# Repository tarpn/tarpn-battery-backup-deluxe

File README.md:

# TARPN Battery Backup Deluxe

An open source DC-DC Uninterrupted Power Supply for TARPN. 

📖 Click here for [Operation Manual](https://github.com/tarpn/tarpn-battery-backup-deluxe/wiki/Operation-Manual) 📖

Battery Backup Deluxe (BBD) is a system that monitors and switches DC power between a 
power supply and a battery. It is a bespoke power management solution for multi-port packet
radio nodes in the [TARPN project](http://tarpn.net). It is also generally useful for any 12V
systems including non-TARPN Amateur Radio activities.

Supported Features:
* High current capability (30A continuous)
* Automatic switchover to battery
* Battery protection (low/high voltage cutoff)
* Over-temperature cutoff
* Separate switching of critical loads power for priority devices (3A max)
* Safe shutdown procedure of RaspberryPi

Experimental Features:
* Battery charging

Non-Features:
* Load distribution or fusing
* Integration with battery chargers (AC/DC chargers, or solar charge controllers)

Two custom PCBs are employed for voltage sensing, switching, and control. The two boards are
referred to as the Power Board and the Control Board. The Power Board connects to a regulated
DC power supply, a 12V battery, a 12V load, a DC buck regulator for a RaspberryPi, and the Control Board. 
The Control Board connects to a RaspberryPi using a communication cable. 

# Images

Power Board, bare PCB

Power Board, assembled and installed

# PCB Overview

Power board layout

```
 -[B]--[L]--[S]--[N]--[N]--[N]-
|  |    |    |                 |
|  |~S2~ ~S1~               [C]|
|  |                           |
|   ~ ~ ~ ~ ~ ~ ~ ~ ~ ~ S3     |
|                        |     |
 -----------------------[P][N]-
```

Labels:

* B: Battery Positive
* S: Supply Positive
* L: Load Positive
* N: Common Grounds
* P: Critical Load Positive
* S1: Supply Switch
* S2: Battery Switch
* S3: Critical Load Switch
* C: 12-pin connector to control board

Three p-channel mosfet switches are utilized to connect various loads to one of two DC power sources. 
Loads connected to the "L" terminal are either connected to the Power Supply "S" via S1, the Battery 
"B" via S2, or they are disconnected. A separate low power switch S3 is used for critical loads, 
such as a RaspberryPi or other low power control circuits.

S1 and S2 are high powered DPAK mosfets with a very low on-resistance.

All connected supplies and loads share a common ground. This ground is also shared with the control board. 
If a RaspberryPi (or other device) is monitoring the serial output of the control board, it must also share
this common ground.

Control board layout

```
 ------------------------------
|         ___________      ___  |
|[C]     |   OLED    |    | R | |
|         -----------      ---  |
|    [RPi]               [ICSP] |
 ------------------------------
```

Labels:

* C: 12-pin connector to power board
* RPi: 10-pin connector to Raspberry Pi
* ICSP: Programming header for ATMega
* OLED: 128x32 OLED display
* R: Rotary encoder with switch

# Control Board Modes

The digital electronics on the power board, the 5V regulator for the Control Board, and the critical load
output are powered directly by the battery. 

## Standby

When a power supply is attached and supplying a sufficient voltage, the system will be in Standby mode. 
Loads are powered by the power supply through S1.

* S1: closed
* S2: open
* S3: closed

## Backup

If a low voltage is detected on the power supply, the loads are transferred to the battery. This switching
time is typically in the microsecond range. The ability of the loads to maintain sufficient voltage during
the switching time is dependent on the load current and the available standby capacitance. 
C1 on the power board can be populated with a reasonably large (1000µF range) bulk capacitor. 

* S1: open 
* S2: closed
* S3: closed

## Recovery

Once in the Backup state, the system will enter the Recovery state if a sufficient voltage is seen at the
power supply input. To avoid oscillations, the system will remain in the Recovery state for a configured
number of milliseconds before transitioning to Standby.

* S1: open 
* S2: closed
* S3: closed

## Faults

The system monitors battery voltage to protect the loads from over-voltage and to protect the battery from
under-voltage. In these two cases, the battery is disconnected from the loads.

A temperature sensor is used to monitor the temperature of the PCB near the mosfet switches. If a high
temperature is detected, the switches are both opened to prevent the mosfets from over-heating and failing.

* S1: open 
* S2: open
* S3: closed

# Tuning

To account for variability of components used by the sensor circuits, the firmware includes several "tunables".

* X1: Current Sense. A scaling factor for the current shunt resistor R3. It should be set to 0.04 (20 * R3)
* X2: Current Offset. A voltage offset provided by the reference voltage U1. It should be set to 2.486
* X3: ADC Reference. A voltage reference provided by U5. Measured from AREF (typically 4.860)
* X4: Voltage Factor. A scaling factor for the two resistor divider networks R1+R4 and R8+R11. It should be set to R4 / (R1 + R4).
* X5: Voltage Offset. A voltage offset for the resistor divider networks. Set this to 0.0
* X6: Battery Factor. The same as X1, but for R36 (this may be deprecated in the future)
* X7: Battery Offset. The same as X2, but for the battery current shunt (this may be deprecated in the future)

# Configuration

TODO

# RaspberryPi Interface

J8 on the control board connects to pins 1 through 10 on the RaspberryPi. 

| Pin | RPi signal | Control board signal |
| --- | ---------- | -------------------- |
| 1   | +3V3       | used for pullup of pin 5 |
| 2   | +5V        | unused |
| 3   | GPIO 2     | RPI_PWR (active low) |
| 4   | +5V        | unused |
| 5   | GPIO 3     | RPI_SHUTDOWN (active low) |
| 6   | Ground     | Ground |
| 7   | GPIO 4     | Reset† |
| 8   | GPIO 14    | RXD (serial) |
| 9   | Ground     | Ground |
| 10  | GPIO 15    | TXD (serial) |

† This pin is sometimes cut on older TARPN installations. See below for workaround instructions.

The RPI_SHUTDOWN signal is used to trigger a shutdown of the RPi. When this signal is momentarily pulled low the RPi 
will perform a safe shutdown. A pull-up resistor between RPi pin 5 and RPi pin 1 is used to prevent this
signal from floating.

The RPI_PWR is used to inform the control board whether or not the RPi has power. When this signal is
low, the RPi is powered on. This signal allows the control board to determine when the RPi has powered off 
following a safe shutdown.

RXD and TXD are used for serial communication from the control board to the RPi. This is used for exporting
telemetry from the control board.

If pin 7 has been cut, a separate jumper between an unused GPIO on the RPi and the RESET line on the control 
board will be needed. Pin 5 of the ISCP header can be used to solder one end of a jumper. When doing firmware
uploads from the RPi, a different reset pin can be selected with the `--gpio` argument.

## RPi Hardware Modification

To accommodate the 10 pin ribbon connector on the RPi, pins 11 and 12 must be snipped or bent out of the way.

## RPi Hardware Configuration

To enable the functions of RPI_SHUTDOWN and RPI_PWR, two special configurations are needed on the RPi.
In the `/boot/config.txt` file, add the following lines below the comment 
`# Additional overlays and parameters are documented /boot/overlays/README`:

```
dtoverlay=gpio-poweroff,gpiopin=2,active_low=1
dtoverlay=gpio-shutdown,gpio_pin=3,active_low=1,gpio_pull=up
```

The hardward UART must also be enabled for communication with the control board. At the bottom of `/boot/config.txt`, add

```
[all]
enable_uart=1
```

This can be done when preparing the SD card or on a running RPi. If done on a running RPi, a reboot is necessary for the 
changes to take affect.

## RPi Software Setup

Assuming a starting point of Raspberry Pi OS (Debian Bullseye or Bookworm), we need to install a few dependencies.

```
sudo apt-get -y install python3-pip python3-venv supervisor prometheus prometheus-node-exporter lsof avrdude
```

Configure supervisor to be run as the "pi" user. Modify the file `/etc/supervisor/supervisord.conf` to add a "chown"
to the "unix_http_server" section:

```
[unix_http_server]
file=/var/run/supervisor.sock   ; (the path to the socket file)
chmod=0700                      ; sockef file mode (default 0700)
chown=pi:pi                     
```

Restart supervisor service
```
sudo service supervisor restart
```

Confirm supervisor is running and accessible

```
supervisorctl pid
```

Should return the PID (Process ID) of the supervisord program.

### Install tarpn-bbd Python package

Create an installation directory under `/opt` and install a Python environment into it.

_These instructions assume an installation directory of /opt/tarpn. However, the software can be installed at any location_

```
sudo mkdir /opt/tarpn
sudo chown pi:pi /opt/tarpn
python3 -m venv /opt/tarpn
```

Install the `tarpn-bbd-agent` program into the newly created Python environment

```
/opt/tarpn/bin/pip install --upgrade --index-url https://pypi.mumrah.synology.me/simple tarpn-bbd-agent
```

This will install the program and create several directories under `/opt/tarpn`. 

### Configure Supervisor

Once the tarpn-bbd Python package is installed, we can copy a supervisor config into the system's
configuration directory. This will allow for the Python program to be automatically run on RPi startup
and automatically restarted if it encounters a fatal error.

```
sudo cp /opt/tarpn/extra/tarpn-bbd-agent-supervisor.conf /etc/supervisor/conf.d/tarpn-bbd-agent.conf
```

This file tells supervisor how to run the tarpn-bbd-agent program. Issue a "reload" command to tell
supervisor to read this new config file

```
supervisorctl reload
```

Now the agent program should be running. Run "supervisorctl status" to confirm. The output should look like:

```
> supervisorctl status
tarpn-bbd-agent                  RUNNING   pid 15487, uptime 0:00:04
```

Check that the metrics are being exposed over HTTP. Visit http://localhost:9000 on the RPi, or http://<your-rpi-ip-address>:9000
from another computer on your network. You should see a plain text output that looks like:

```
# HELP python_gc_objects_collected_total Objects collected during gc
# TYPE python_gc_objects_collected_total counter
python_gc_objects_collected_total{generation="0"} 327.0
python_gc_objects_collected_total{generation="1"} 81.0
python_gc_objects_collected_total{generation="2"} 0.0
```

Next, check that the node metrics are being exposed by the prometheus-node-exporter. Visit http://localhost:9100
or http://<your-rpi-ip-address>:9100. This will have a lot more output than the other exporter. Here is a snippet

```
# HELP node_cpu_seconds_total Seconds the CPUs spent in each mode.
# TYPE node_cpu_seconds_total counter
node_cpu_seconds_total{cpu="0",mode="idle"} 2883.87
node_cpu_seconds_total{cpu="0",mode="iowait"} 5.04
node_cpu_seconds_total{cpu="0",mode="irq"} 0
node_cpu_seconds_total{cpu="0",mode="nice"} 0
node_cpu_seconds_total{cpu="0",mode="softirq"} 0.95
node_cpu_seconds_total{cpu="0",mode="steal"} 0t
node_cpu_seconds_total{cpu="0",mode="system"} 11.35
node_cpu_seconds_total{cpu="0",mode="user"} 22.08
```

### Python Configuration

The default configuration should work on most installations, but if a different serial port or HTTP port is needed, 
it can be changed in `/opt/tarpn/config/bbd.ini`

```
[default]
log.dir = /opt/tarpn/logs
log.config = config/logging.ini
serial.port = /dev/ttyS0
serial.speed = 38400
prometheus.port = 9000
```

After re-configuring, restart the service with supervisor

```
supervisorctl restart tarpn-bbd-agent
```

# Monitoring

If desired, a metrics collection database (Prometheus) and dashboard system (Grafana) can be used to visualize
the sensor data exported by the control board.

Prometheus needs network access to the RPi running `tarpn-bbd`, and Grafana needs network access to Prometheus.
On a home network, this is usually achieved without any extra effort. It is possible to run the TARPN stack 
(including `tarpn-bbd`) along with Prometheus and Grafana, but it is also possible to run Prometheus and Grafana
on a separate server if resources of the RPi become constained.

## Prometheus Configuration

Prometheus is an efficient time-series database that is optimized for metrics collection. By default, Prometheus 
is installed on the RPi that is also running TARPN and the Python agent. If desired, Prometheus can also be 
installed on another server (RPi or otherwise). Follow the 
[general installation instructions](https://prometheus.io/docs/prometheus/latest/installation/) for this.

Put the prometheus config in place

```
sudo cp /opt/tarpn/extra/prometheus.yml /etc/prometheus/prometheus.yml
```

And restart prometheus

```
sudo service prometheus restart
```

Launch the Prometheus UI and confirm the three targets are "UP". Load the UI by accessing http://localhost:9090 
on a web browser on the RPi, or http://<your-rpi-ip-address>:9090 from a web browser on another computer in your
network.

Click on Status, then Targets

And the three Targets should be in the "UP" State.

## Grafana Install and Configuration

Follow the instructions to [install Grafana OSS](https://grafana.com/tutorials/install-grafana-on-raspberry-pi/#install-grafana).
Grafana can run on the TARPN RPi or on a separate server (RPi or otherwise).

For other installation types, follow the [general installation instructions](https://grafana.com/docs/grafana/latest/setup-grafana/installation/).

Copy some configuration files from the `tarpn-bbd` installation over to Grafana

```
sudo cp /opt/tarpn/extra/grafana.ini /etc/grafana/grafana.ini
sudo cp /opt/tarpn/extra/prometheus-datasource.yml /etc/grafana/provisioning/datasources/prometheus.yml
```

Enable Grafana service (as indicated the Grafana installation output). This will enable Grafana to start
when the RPi starts.

```
sudo /bin/systemctl daemon-reload
sudo /bin/systemctl enable grafana-server
```

Start Grafana (restart if it's already running)
```
sudo service grafana restart
```

Access the Grafana UI at http://localhost:3000 or `http://<your-rpi-ip-address>:3000`. 

Confirm the "prometheus" datasource was created

https://github.com/tarpn/tarpn-battery-backup-deluxe/assets/55116/4cb37a2d-a11b-4c16-b97d-481c0bf3d614

Next, import the dashboard

* Open https://github.com/tarpn/tarpn-battery-backup-deluxe/blob/main/py/extra/grafana-dashboard.json
* Click "Download Raw File"
* Open Grafana UI
* Navigate to Dashboards
* Click New -> Import
* Select the dashboard JSON file
* Select the "Prometheus" datasource we looked at earlier

https://github.com/tarpn/tarpn-battery-backup-deluxe/assets/55116/16305afa-259e-4ca9-8b7f-3a017b2bc0ff

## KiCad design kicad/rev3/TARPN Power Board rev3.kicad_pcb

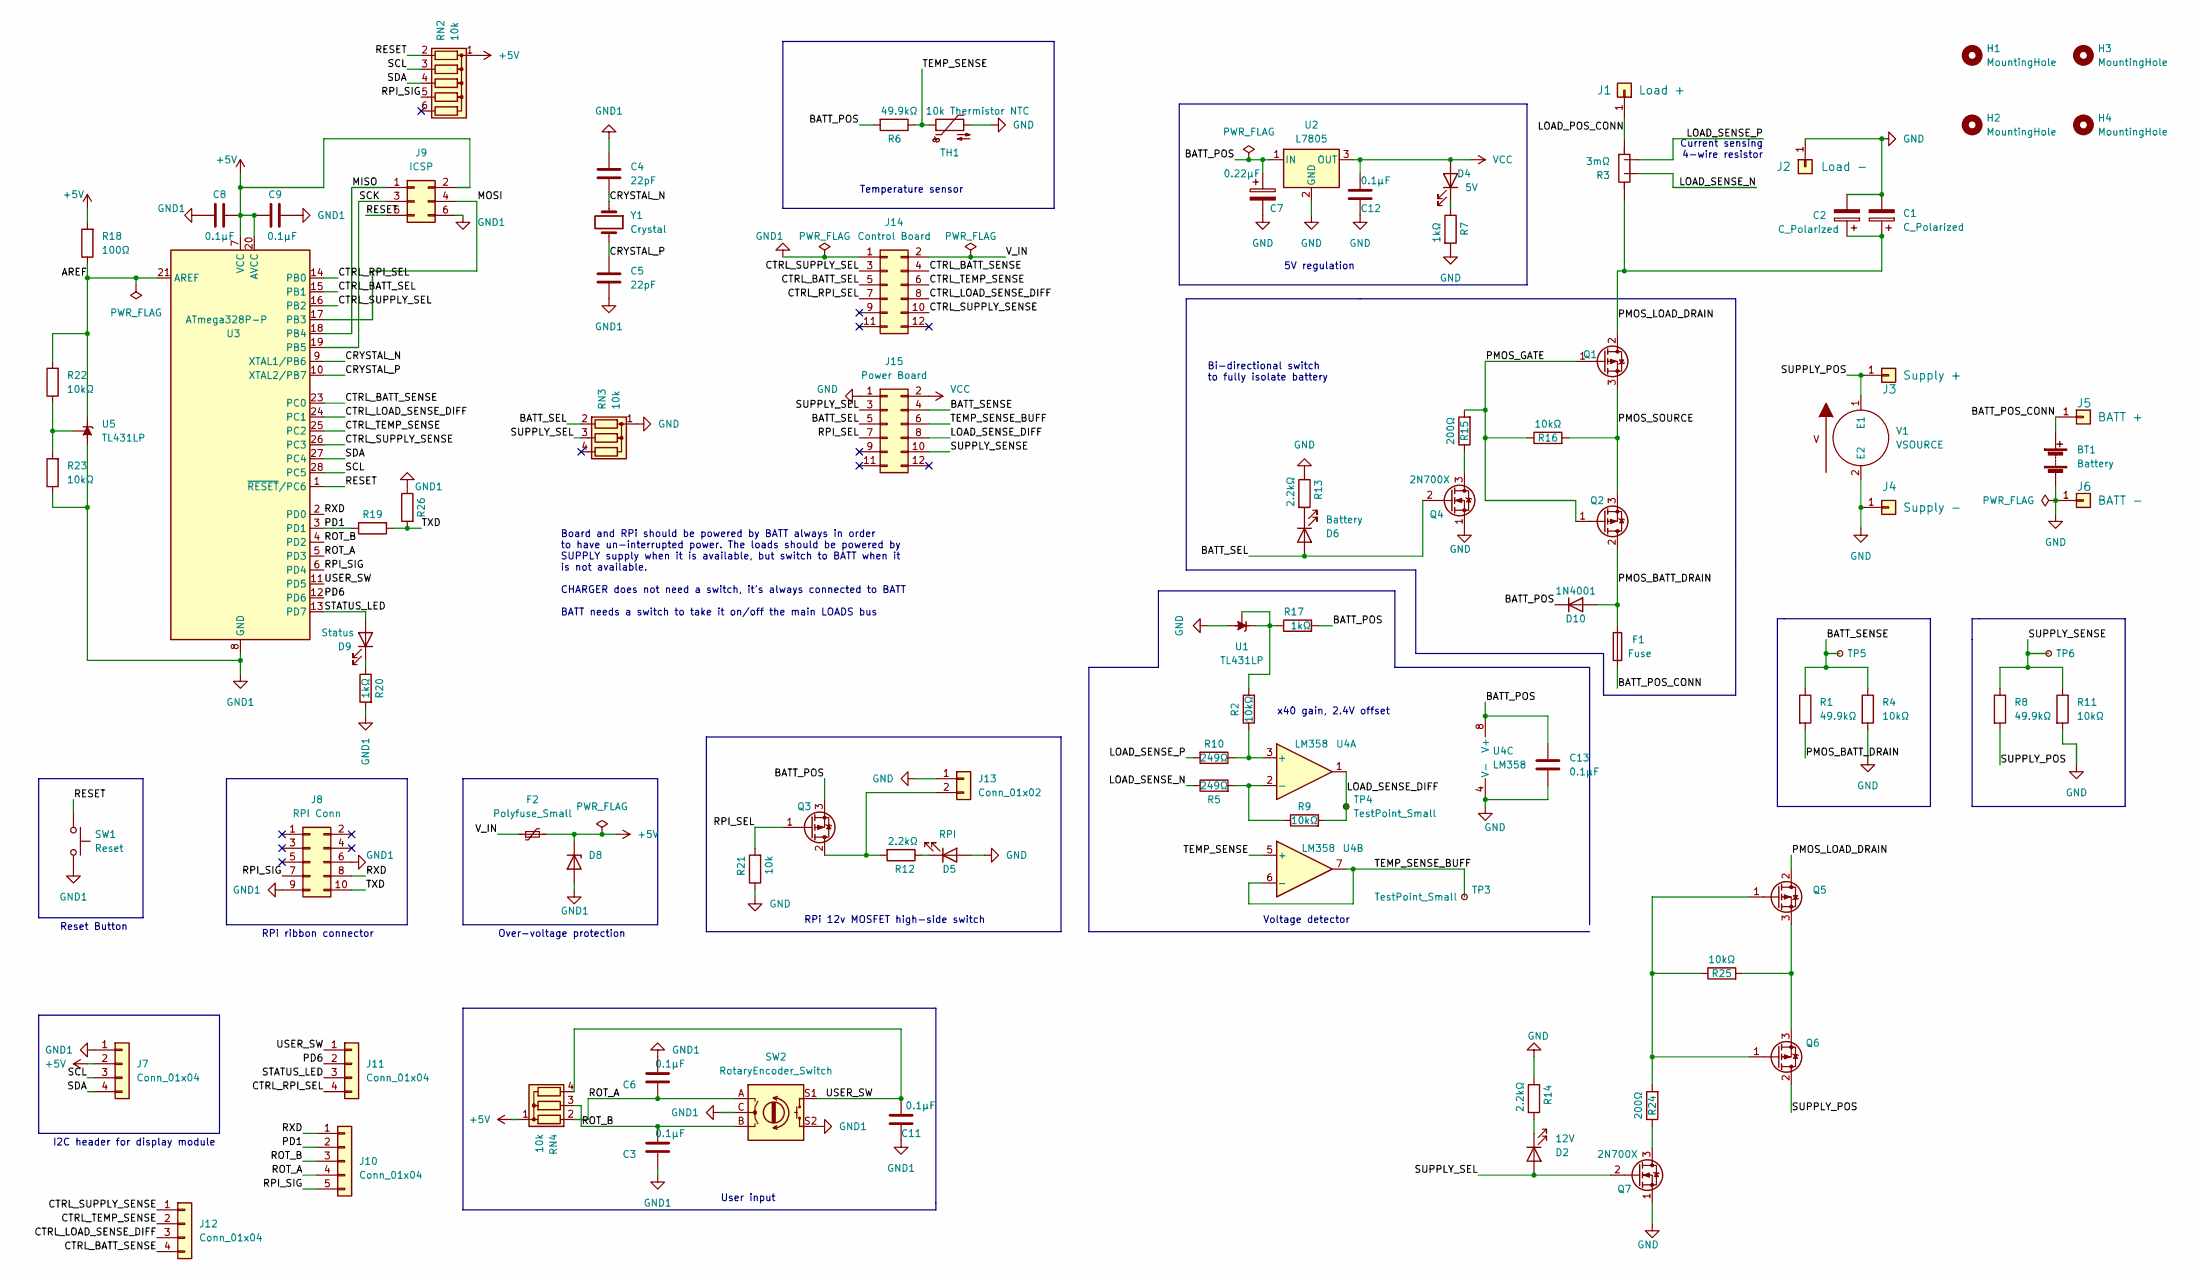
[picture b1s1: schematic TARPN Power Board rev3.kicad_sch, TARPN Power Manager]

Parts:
BT1: Battery
C1, C2: C_Polarized; CP_Radial_D6.3mm_P2.50mm
C3, C6, C8, C9, C11, C12, C13: 0.1µF; C_Disc_D3.0mm_W2.0mm_P2.50mm
C4, C5: 22pF; C_Disc_D3.0mm_W2.0mm_P2.50mm
C7: 0.22µF; CP_Radial_D5.0mm_P2.50mm
D2: 12V; LED_D3.0mm
D4: 5V; LED_D3.0mm
D5: RPI; LED_D3.0mm
D6: Battery; LED_D3.0mm
D8: D_DO-41_SOD81_P3.81mm_Vertical_KathodeUp
D9: Status; LED_D3.0mm
D10: 1N4001; D_DO-41_SOD81_P10.16mm_Horizontal
F1: Fuse; JCASE
F2: Polyfuse_Small; Littlefuse RXEF Series
H1, H2, H3, H4: MountingHole; MountingHole_4.3mm_M4
J1: Load +; B6A-PCB-RS
J2: Load -; B6A-PCB-RS
J3: Supply +; B6A-PCB-RS
J4: Supply -; B6A-PCB-RS
J5: BATT +; B6A-PCB-RS
J6: BATT -; B6A-PCB-RS
J7, J11, J12: Conn_01x04; PinHeader_1x04_P2.54mm_Vertical
J8: RPI Conn; PinHeader_2x05_P2.54mm_Vertical
J9: ICSP; IDC-Header_2x03_P2.54mm_Vertical
J10: Conn_01x04; PinHeader_1x05_P2.54mm_Vertical
J13: Conn_01x02; 691213510002
J14: Control Board; IDC-Header_2x06_P2.54mm_Vertical
J15: Power Board; IDC-Header_2x06_P2.54mm_Vertical
Q1, Q2, Q5, Q6: IRF4905; TO-252-2-ViasHandSolder
Q3: IRF9Z24; TO-220-3_Vertical
Q4, Q7: 2N700X; TO-92_HandSolder
R1, R6, R8: 49.9kΩ; R_Axial_DIN0207_L6.3mm_D2.5mm_P10.16mm_Horizontal
R2, R4, R9, R11, R16, R22, R23, R25: 10kΩ; R_Axial_DIN0207_L6.3mm_D2.5mm_P10.16mm_Horizontal
R3: 3mΩ; R_2512_6332_4_wire
R5, R10: 249Ω; R_Axial_DIN0207_L6.3mm_D2.5mm_P10.16mm_Horizontal
R7, R17, R20: 1kΩ; R_Axial_DIN0207_L6.3mm_D2.5mm_P10.16mm_Horizontal
R12, R13, R14: 2.2kΩ; R_Axial_DIN0207_L6.3mm_D2.5mm_P10.16mm_Horizontal
R15, R24: 200Ω; R_Axial_DIN0207_L6.3mm_D2.5mm_P10.16mm_Horizontal
R18: 100Ω; R_Axial_DIN0207_L6.3mm_D2.5mm_P10.16mm_Horizontal
R19, R26: R_Axial_DIN0207_L6.3mm_D2.5mm_P10.16mm_Horizontal
R21: 10k; R_Axial_DIN0207_L6.3mm_D2.5mm_P10.16mm_Horizontal
RN2: 10k; R_Array_SIP6
RN3, RN4: 10k; R_Array_SIP4
SW1: Reset; SW_PUSH_6mm
SW2: RotaryEncoder_Switch; RotaryEncoder_Alps_EC11E-Switch_Vertical_H20mm
TH1: 10k Thermistor NTC; R_Axial_DIN0204_L3.6mm_D1.6mm_P5.08mm_Horizontal
TP3, TP4, TP5, TP6: TestPoint_Small; TestPoint_THTPad_D1.5mm_Drill0.7mm
U1, U5: TL431LP; TO-92_Inline_Wide
U2: L7805; TO-220-3_Vertical
U3: ATmega328P-P; DIP-28_W7.62mm
U4: LM358
V1: VSOURCE
Y1: Crystal; Crystal_HC49-4H_Vertical

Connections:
+5V: C8.1, C9.2, D8.1 (K), F2.2, J7.2, J9.2, R18.2, RN2.1 (common), RN4.1 (common), U3.7 (VCC), U3.20 (AVCC)
/AREF: R18.1, R22.2, U3.21 (AREF), U5.3 (K)
/BATT_POS: C7.1, C13.2, D10.1 (K), Q3.3 (S), R6.2, R17.2, U2.1 (IN), U4.8 (V+)
/BATT_POS_CONN: BT1.1 (+), F1.2, J5.1
/BATT_SEL: D6.2 (A), J15.5, Q4.2 (G), RN3.2 (R1)
/BATT_SENSE: J15.4, R1.1, R4.1, TP5.1
/CRYSTAL_N: C4.2, U3.9 (XTAL1/PB6), Y1.1
/CRYSTAL_P: C5.1, U3.10 (XTAL2/PB7), Y1.2
/CTRL_BATT_SEL: J14.5, U3.15 (PB1)
/CTRL_BATT_SENSE: J12.4, J14.4, U3.23 (PC0)
/CTRL_LOAD_SENSE_DIFF: J12.3, J14.8, U3.24 (PC1)
/CTRL_RPI_SEL: J11.4, J14.7, U3.14 (PB0)
/CTRL_SUPPLY_SEL: J14.3, U3.16 (PB2)
/CTRL_SUPPLY_SENSE: J12.1, J14.10, U3.26 (PC3)
/CTRL_TEMP_SENSE: J12.2, J14.6, U3.25 (PC2)
/LOAD_POS_CONN: J1.1, R3.1
/LOAD_SENSE_DIFF: J15.8, R9.2, TP4.1, U4.1
/LOAD_SENSE_N: R3.4, R5.1
/LOAD_SENSE_P: R3.3, R10.2
/MISO: J9.1, U3.18 (PB4)
/MOSI: J9.4, U3.17 (PB3)
/PD1: J10.2, R19.1, U3.3 (PD1)
/PD6: J11.2, U3.12 (PD6)
/PMOS_BATT_DRAIN: D10.2 (A), F1.1, Q2.2 (D), R1.2
/PMOS_GATE: Q1.1 (G), Q2.1 (G), R15.2, R16.1
/PMOS_LOAD_DRAIN: C1.1, C2.1, Q1.2 (D), Q5.2 (D), R3.2
/PMOS_SOURCE: Q1.3 (S), Q2.3 (S), R16.2
/RESET: J9.5, RN2.2 (R1), SW1.1, U3.1 (~RESET/PC6)
/ROT_A: C6.2, J10.4, RN4.2 (R1), SW2.A, U3.5 (PD3)
/ROT_B: C3.1, J10.3, RN4.3 (R2), SW2.B, U3.4 (PD2)
/RPI_SEL: J15.7, Q3.1 (G), R21.2
/RPI_SIG: J8.7, J10.5, RN2.5 (R4), U3.6 (PD4)
/RXD: J8.8, J10.1, U3.2 (PD0)
/SCK: J9.3, U3.19 (PB5)
/SCL: J7.3, RN2.3 (R2), U3.28 (PC5)
/SDA: J7.4, RN2.4 (R3), U3.27 (PC4)
/STATUS_LED: D9.2 (A), J11.3, U3.13 (PD7)
/SUPPLY_POS: J3.1, Q6.2 (D), R8.2, V1.1 (E1)
/SUPPLY_SEL: D2.2 (A), J15.3, Q7.2 (G), RN3.3 (R2)
/SUPPLY_SENSE: J15.10, R8.1, R11.1, TP6.1
/TEMP_SENSE: R6.1, TH1.1, U4.5 (+)
/TEMP_SENSE_BUFF: J15.6, TP3.1, U4.6 (-), U4.7
/TXD: J8.10, R19.2, R26.2
/USER_SW: C11.1, J11.1, RN4.4 (R3), SW2.S1, U3.11 (PD5)
/V_IN: F2.1, J14.2
GND: BT1.2 (-), C1.2, C2.2, C7.2, C12.1, C13.1, D5.2 (A), J2.1, J4.1, J6.1, J13.1, J15.1, Q4.1 (S), Q7.1 (S), R4.2, R7.2, R11.2, R13.1, R14.1, R21.1, RN3.1 (common), TH1.2, U1.2 (A), U2.2 (GND), U4.4 (V-), V1.2 (E2)
GND1: C3.2, C4.1, C5.2, C6.1, C8.2, C9.1, C11.2, D8.2 (A), J7.1, J8.6, J8.9, J9.6, J14.1, R20.2, R23.1, R26.1, SW1.2, SW2.C, SW2.S2, U3.8 (GND), U3.22 (GND), U5.2 (A)
unnamed: D2.1 (K), R14.2
unnamed: D4.1 (K), R7.1
unnamed: D5.1 (K), R12.1
unnamed: D6.1 (K), R13.2
unnamed: D9.1 (K), R20.1
unnamed: J13.2, Q3.2 (D), R12.2
unnamed: Q4.3 (D), R15.1
unnamed: Q5.1 (G), Q6.1 (G), R24.2, R25.1
unnamed: Q5.3 (S), Q6.3 (S), R25.2
unnamed: Q7.3 (D), R24.1
unnamed: R5.2, R9.1, U4.2 (-)
unnamed: R2.1, R10.1, U4.3 (+)
unnamed: R2.2, R17.1, U1.1 (REF), U1.3 (K)
unnamed: R22.1, R23.2, U5.1 (REF)
VCC: C12.2, D4.2 (A), J15.2, U2.3 (OUT)

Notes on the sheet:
I2C header for display module
Bi-directional switch to fully isolate battery
RPi 12v MOSFET high-side switch
RPi ribbon connector
Reset Button
Board and RPi should be powered by BATT always in order to have un-interrupted power. The loads should be powered by SUPPLY supply when it is available, but switch to BATT when it is not available. CHARGER does not need a switch, it's always connected to BATT BATT needs a switch to take it on/off t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
5V regulation
Temperature sensor
Over-voltage protection
x40 gain, 2.4V offset
Current sensing 4-wire resistor
Voltage detector
User input

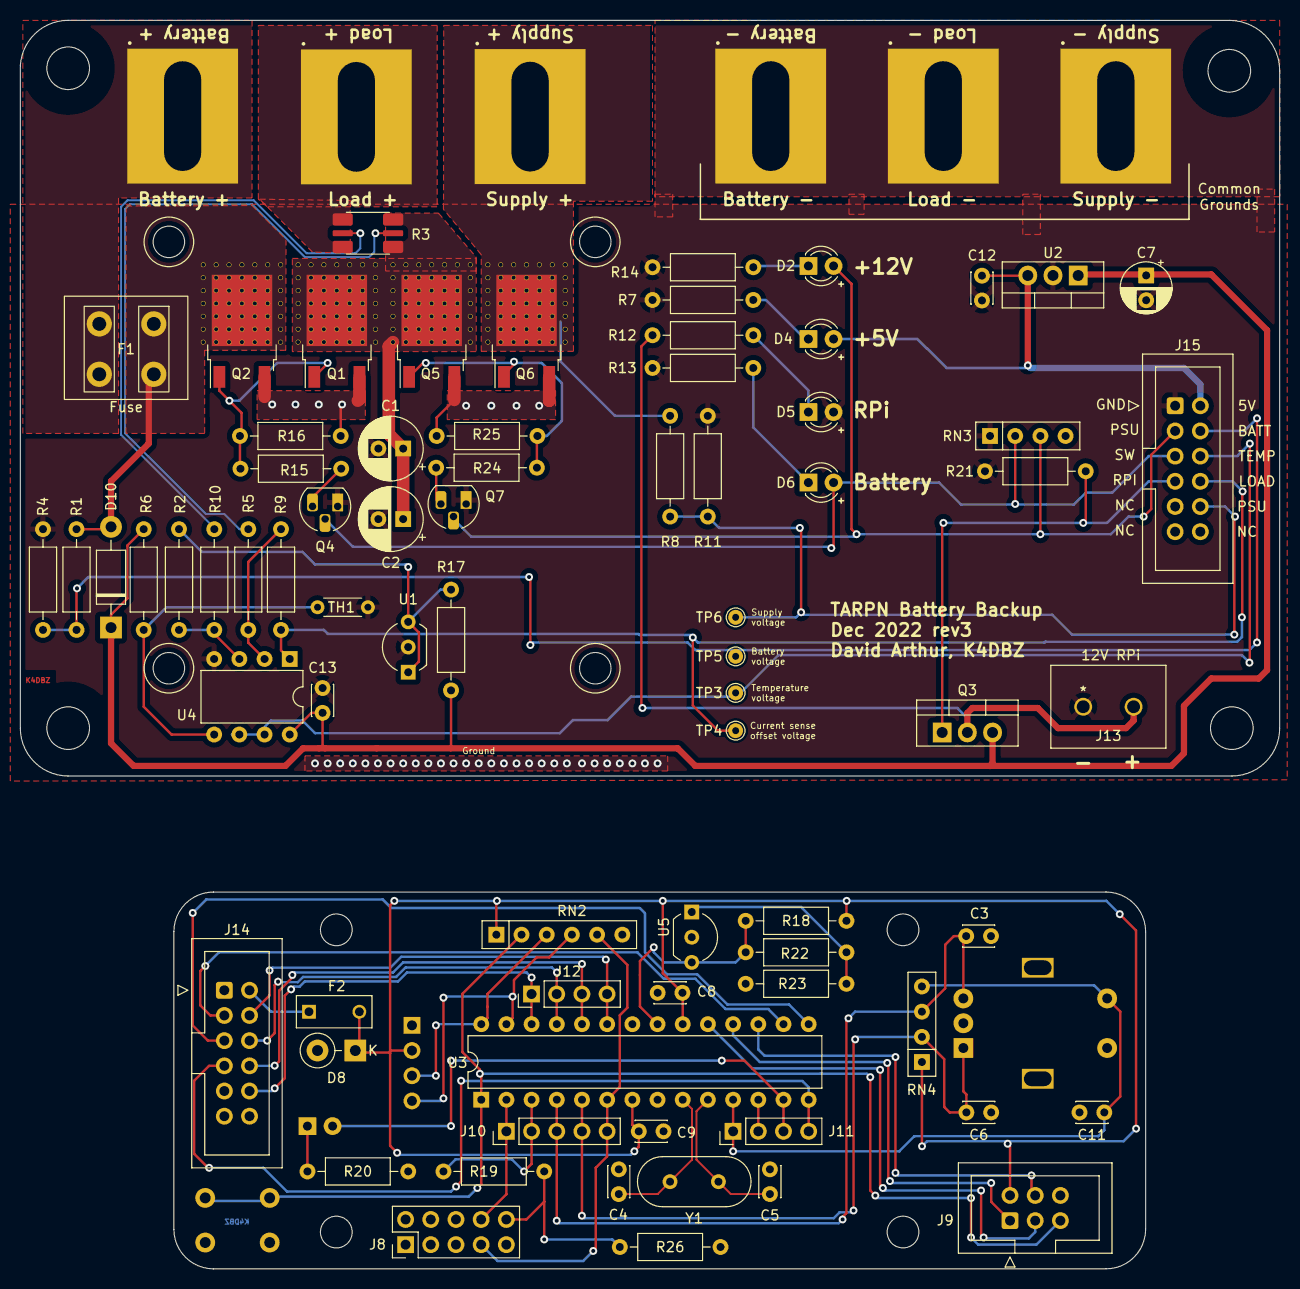
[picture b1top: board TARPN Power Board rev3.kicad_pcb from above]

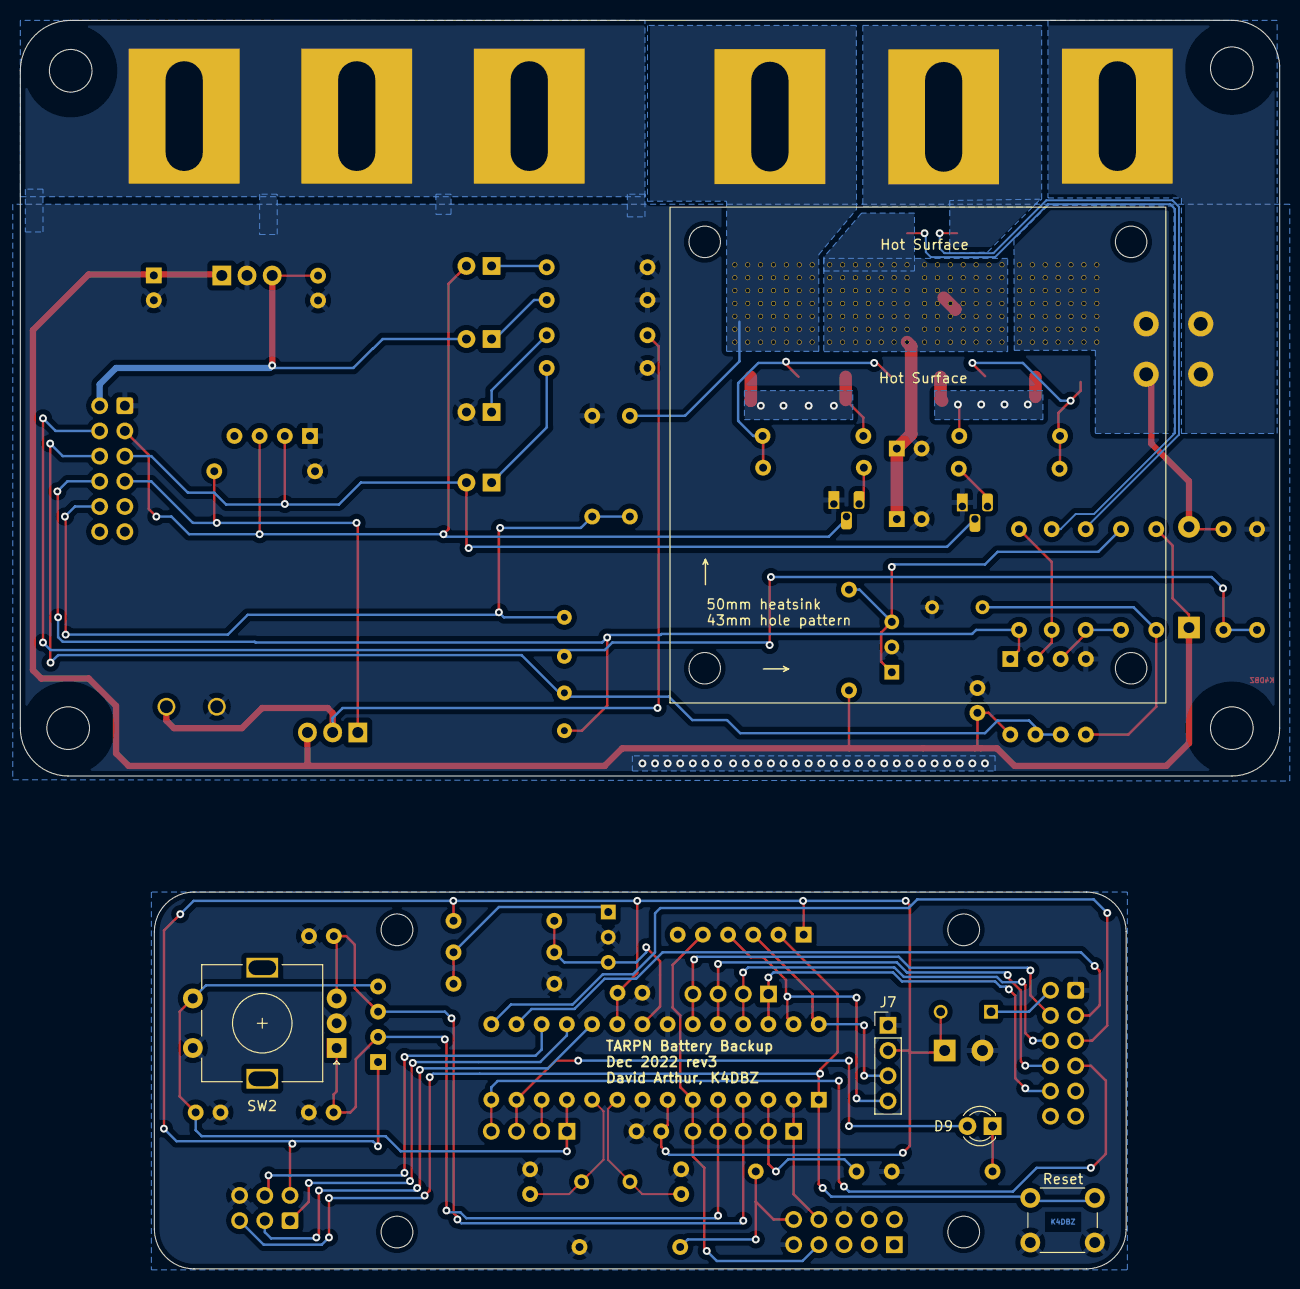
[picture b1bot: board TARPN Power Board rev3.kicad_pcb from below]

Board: 2 copper layers, 127.0 x 125.9 mm, 89 parts (4 on the bottom side), 62 nets.

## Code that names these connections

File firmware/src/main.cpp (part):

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#include "batt.h"

#define RPI_POWEROFF_PIN 4  // pulled high, low, high when RPi is ready for power off 
#define STATUS_LED 7
#define RPI_PWR_PIN 8
#define BATTERY_PIN 5
#define SUPPLY_PIN 19
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  cbi(ADMUX, REFS1);

  sbi(PCICR, PCIE0);        // Enable pin change interrupts on port b
  sbi(PCMSK0, PCINT4);      // Set pin change mask for PB4 (D12, pin 18, MISO)

  sbi(PCICR, PCIE2);        // Enable pin change interrupts on port d
  sbi(PCMSK2, PCINT22);     // Set pin change mask for PD6

  // Timer1 for ADC sampling
  // http://www.8bit-era.cz/arduino-timer-interrupts-calculator.html
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  sei();

  pinMode(RPI_POWEROFF_PIN, INPUT_PULLUP);
  pinMode(STATUS_LED, OUTPUT);
  pinMode(BATTERY_PIN, OUTPUT);  
  pinMode(SUPPLY_PIN, OUTPUT);  
  pinMode(RPI_PWR_PIN, OUTPUT);
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  last_heartbeat = 0L;

  //user_sw = Bounce();
  //user_sw.attach(BUTTON_PIN, INPUT);
  //user_sw.interval(BUTTON_PIN);

  PID_Init(&pid_cc, 1.0f, 0.0f);
  PID_Init(&pid_cv, 10.0f, 0.0f);
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
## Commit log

2023-01-03 Changes for rev3 board
2023-01-03 Big memory re-org
    Was seeing problems with errant output on the OLED. Likely due to its buffer
    getting clobbered by other objects in memory. I moved all the static configs
    into PROGMEM and reduced the SRAM used below 1kb. This should leave enough
    space for the 1kb OLED buffer.
    Also added a "print_float" function to work around poor support for floats
    in the SSD1306 library.
2023-01-03 Adding KiCad files and starting on README
2023-01-12 Adding image of rev3 board
2023-02-22 Get RPi shutdown sequence working
    Also add low power mode
2023-03-21 Add python scraper program
2023-03-22 work on readme
2023-03-23 Add images of powerboard
2023-03-23 More images
2023-03-23 add power board back images
2023-03-23 Add heatsink notes
2023-03-23 fix spelling
2023-03-23 more assembly images
2023-03-23 Rename
2023-03-23 Add lug close-ups
2023-03-23 Add terminal lug instructions
2023-06-17 Try to handle load spikes
2023-06-17 Add icons to show current state
2023-08-17 Add ribbon cable to BOM
2023-08-30 Add prometheus install instructions
2023-08-30 Fix screenshot
2023-08-30 Adding some Grafana instructions
2023-08-30 Remove systemd unit, add supervisor
2023-08-30 Rename "bdd" to "bbd" (Battery Backup Deluxe)
2023-08-30 Use tarpn-bbd-scrape for supervisor name
2023-08-30 change default config
2023-08-30 Add new files to egg
2023-08-30 Rename dashboard file
2023-08-30 Add grafana files
2023-08-30 Add some configs
2023-08-30 fix packaging
2023-09-07 Use Editor role for anonymous
2023-09-07 Don't send negative current values to Prometheus
2023-09-08 Switch from AH to PowerAvg field from control board output
2023-09-08 Collect uptime
2023-09-09 Update dashboard with serial chart
2023-09-11 set protocol for sparkfun programmer
2023-09-11 Serial speed at 115200
2023-09-11 Typo
2024-04-09 Prepare repository for public
2024-04-09 Create LICENSE for Python code
2024-04-09 Rename LICENSE to py/LICENSE
2024-04-09 add firmware license
2024-04-09 remove old source file
2024-04-11 add STL for terminal guard
2024-06-14 make firmware device configurable
